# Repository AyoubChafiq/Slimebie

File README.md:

# Slimebie
A variation of the Hack Club Starbie, made for Hack Club Half Life. A PCB design including firmware.

Includes a designed silkscreen on one layer, and has few other differences than the primary Starbie
Has 1 extra LED

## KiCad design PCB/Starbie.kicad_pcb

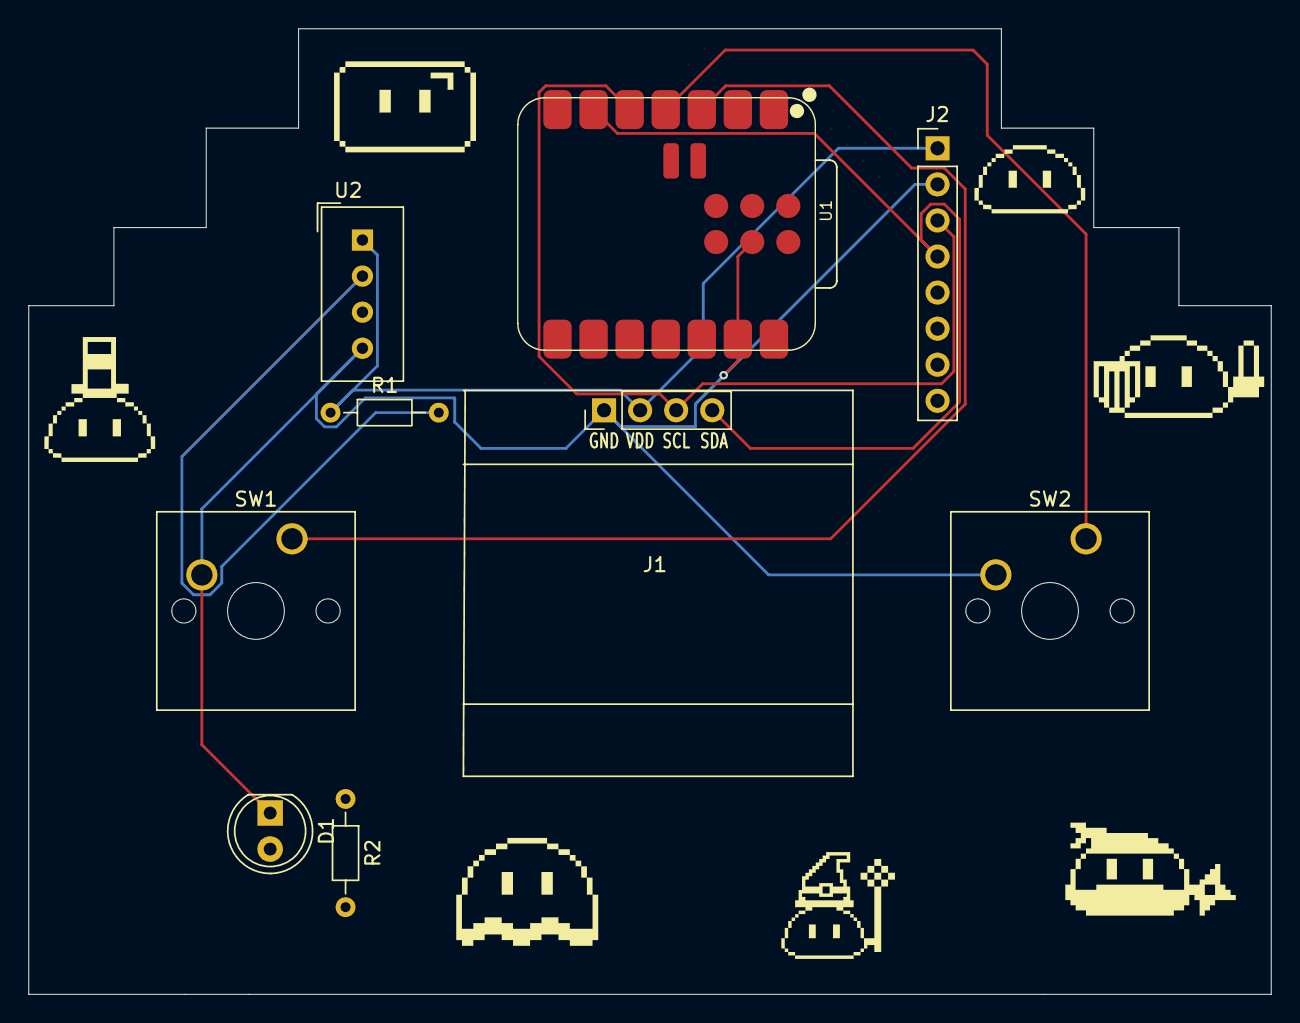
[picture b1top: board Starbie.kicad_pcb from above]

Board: 2 copper layers, 87.5 x 68.0 mm, 9 parts (0 on the bottom side), 7 nets.

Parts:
D1: LED; LED_D5.0mm
J1: Conn_01x04_Pin; Display_128x64_096_I2C
J2: Conn_01x08_Pin; PinHeader_1x08_P2.54mm_Vertical
R1: 10K; R_Axial_DIN0204_L3.6mm_D1.6mm_P7.62mm_Horizontal
R2: 330; R_Axial_DIN0204_L3.6mm_D1.6mm_P7.62mm_Horizontal
SW1, SW2: SW_Push; SW_Cherry_MX_1.00u_PCB
U1: XIAO-ESP32-C3-SMD
U2: DHT11; Aosong_DHT11_5.5x12.0_P2.54mm

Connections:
+3.3V: J1.2, J2.1, R1.1, U1.12 (3V3_OUT), U2.1 (VDD)
/DHT11 DATA: R1.2, U1.2 (D1), U2.2 (DATA)
/GPIO2: SW1.1, U1.3 (D2)
/GPIO3: SW2.1, U1.4 (D3)
/SCL: J1.3, J2.3, U1.5 (D4)
/SDA: J1.4, J2.4, U1.6 (D5)
GND: D1.1 (K_1), J1.1, J2.2, SW1.2, SW2.2, U1.13 (GND), U1.18 (GND), U2.4 (GND)
